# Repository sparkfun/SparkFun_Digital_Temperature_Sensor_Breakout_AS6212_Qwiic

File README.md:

SparkFun Digital Temperature Sensor Breakout - AS6212 (Qwiic)
========================================

[*SparkFun Digital Temperature Sensor Breakout - AS6212 (Qwiic)(SEN-18521)*](https://www.sparkfun.com/products/18521)

The AS6212 provides a combination of high temperature accuracy with excellent low power consumption using the AS6212 digital temperature sensor from ams AG. The AS6212 measures temperature with &plusmn;0.2&deg;C accuracy between -10&deg;C to 65&deg;C, consumes an average of 6&micro;A (0.1&micro;A in standby) and communicates over I<sup>2</sup>C so naturally we put it on a Qwiic breakout to add to our ever expanding Qwiic system. The sensor boasts a host of features including a configurable alert pin that can trigger when temperature data exceeds user-defined temperature thresholds. All of this in a tiny IC package measuring 1.5mm x 1mm.

The AD0 and AD1 jumpers control the I<sup>2</sup>C address as well as enabling/disabling the Alert pin. By default, these two-way jumpers connect the AD0 pin to Ground and the Alert/AD1 pin to 3.3V to enable the Alert pin and set the I<sup>2</sup>C address to 0x48. These jumpers control the address and enable/disable the Alert pin.

Repository Contents
-------------------

* **/Documentation** - Data sheets, additional product information
* **/Hardware** - Eagle design files (.brd, .sch)
* **/Production** - Production panel files (.brd)

Documentation
--------------

* **[Installing an Arduino Library Guide](https://learn.sparkfun.com/tutorials/installing-an-arduino-library)** - Basic information on how to install an Arduino library.
* **[SparkFun AS6212 Qwiic Arduino Library](https://github.com/sparkfun/SparkFun_AS6212_Qwiic_Arduino_Library)** - Arduino library for the SparkFun Digital Temperature Sensor Breakout - AS6212 (Qwiic).
* **[Qwiic AS6212 Py](https://github.com/sparkfun/Qwiic_AS6212_Py)** - Python module for the SparkFun Digital Temperature Sensor Breakout - AS6212 (Qwiic).
* **[Hookup Guide](https://learn.sparkfun.com/tutorials/digital-temperature-sensor-breakout---as6212-qwiic-hookup-guide)** - Basic hookup guide for the SparkFun Digital Temperature Sensor Breakout - AS6212 (Qwiic).

Version History
---------------

* [SEN-18521](https://www.sparkfun.com/products/18521) - Initial release of the SparkFun Digital Temperature Sensor Breakout - AS6212 (Qwiic).

License Information
-------------------

This product is _**open source**_! 

Please review the LICENSE.md file for license information. 

If you have any questions or concerns on licensing, please contact technical support on our [SparkFun forums](https://forum.sparkfun.com/viewforum.php?f=152).

Distributed as-is; no warranty is given.

- Your friends at SparkFun.

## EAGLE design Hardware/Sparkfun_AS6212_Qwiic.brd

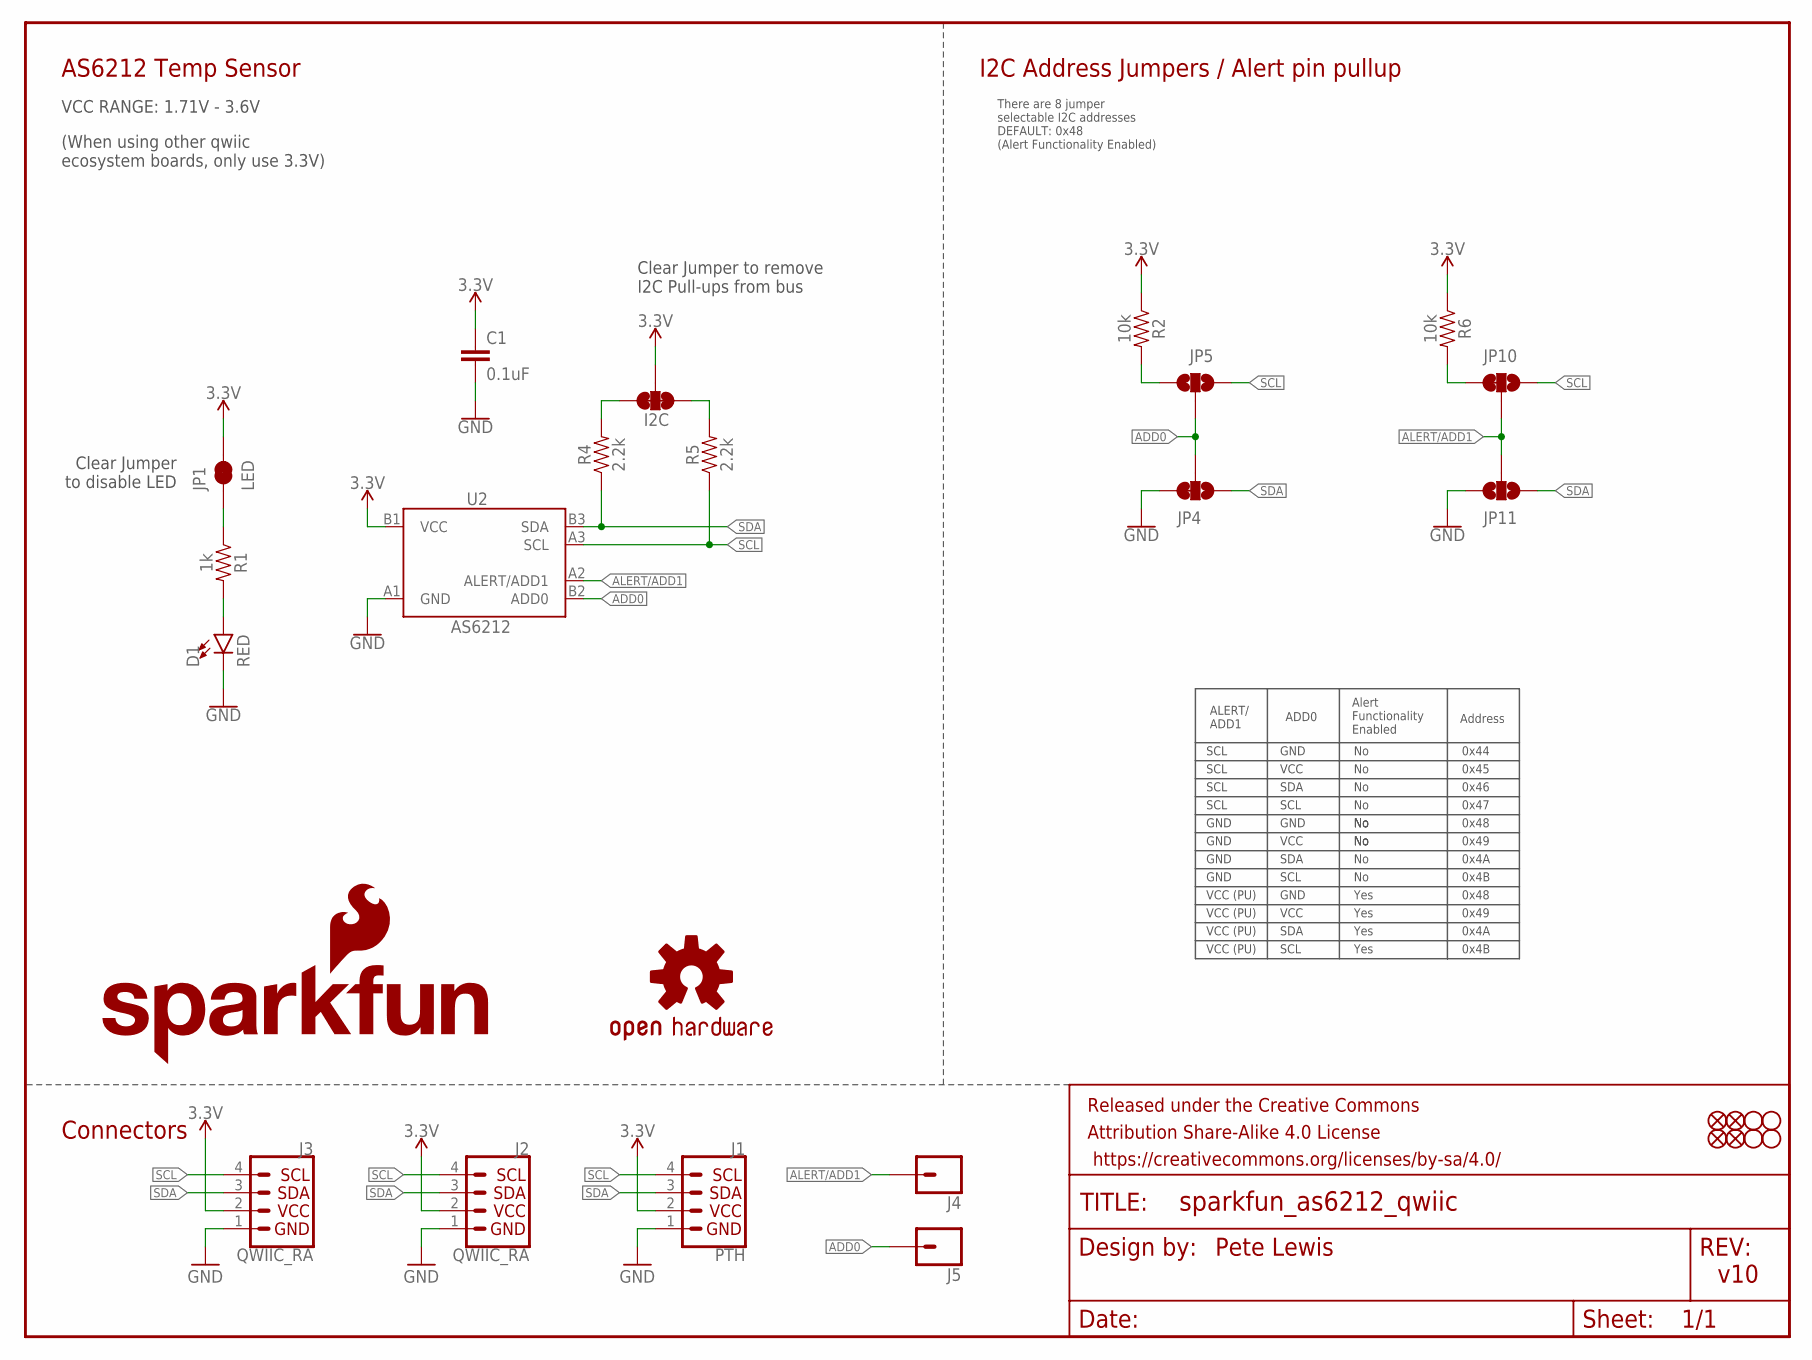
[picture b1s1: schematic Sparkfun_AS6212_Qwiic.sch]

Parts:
C1: 0.1uF; 0603
D1: RED; LED-0603
FD1, FD2, FD3, FD4: FIDUCIALUFIDUCIAL; FIDUCIAL-MICRO
FRAME1: FRAME-LETTER; CREATIVE_COMMONS
I2C: JUMPER-SMT_3_2-NC_TRACE_SILK; SMT-JUMPER_3_2-NC_TRACE_SILK
J1: PTH; 1X04_NO_SILK
J2, J3: QWIIC_RA; JST04_1MM_RA
J4, J5: CONN_01PTH_NO_SILK_YES_STOP; 1X01_NO_SILK
JP1: LED; SMT-JUMPER_2_NC_TRACE_SILK
JP2, JP3, JP8, JP9: STAND-OFF
JP4, JP10: JUMPER-SMT_3_1-NC_TRACE_NO-SILK; SMT-JUMPER_3_1-NC_TRACE_NO-SILK
JP5, JP11: JUMPER-SMT_3_NO_NO_SILK; SMT-JUMPER_3_0-NO_TRACE_NO-SILK
LOGO1: OSHW-LOGOMINI; OSHW-LOGO-MINI
LOGO4: SFE_LOGO_NAME_FLAME.1_INCH; SFE_LOGO_NAME_FLAME_.1
R1: 1k; 0603
R2, R6: 10k; 0603
R4, R5: 2.2k; 0603
U2: AS6212; WLCSP

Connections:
3.3V: C1.1, I2C.2, J1.2, J2.2, J3.2, JP1.2, R2.1, R6.1, U2.B1 (VCC)
ADD0: J5.1, JP4.2, JP5.2, U2.B2 (ADD0)
ALERT/ADD1: J4.1, JP10.2, JP11.2, U2.A2 (ALERT/ADD1)
GND: C1.2, D1.C, J1.1, J2.1, J3.1, JP4.3, JP11.3, U2.A1 (GND)
unnamed: D1.A, R1.2
unnamed: I2C.1, R5.2
unnamed: I2C.3, R4.2
unnamed: JP10.3, R6.2
unnamed: JP5.1, R2.2
unnamed: JP1.1, R1.1
SCL: J1.4, J2.4, J3.4, JP5.3, JP10.1, R5.1, U2.A3 (SCL)
SDA: J1.3, J2.3, J3.3, JP4.1, JP11.1, R4.1, U2.B3 (SDA)

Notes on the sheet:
Pete Lewis
Clear Jumper to remove I2C Pull-ups from bus
v10
There are 8 jumper selectable I2C addresses DEFAULT: 0x48 (Alert Functionality Enabled)
Alert Functionality Enabled
SCL
Clear Jumper to disable LED
VCC RANGE: 1.71V - 3.6V
(When using other qwiic ecosystem boards, only use 3.3V)
AS6212 Temp Sensor
I2C Address Jumpers / Alert pin pullup
Connectors
VCC (PU)
GND
ALERT/ ADD1
ADD0
SDA
VCC
Yes
Address
0x44
0x45
0x46
0x49
0x4A
0x4B
0x47
0x48

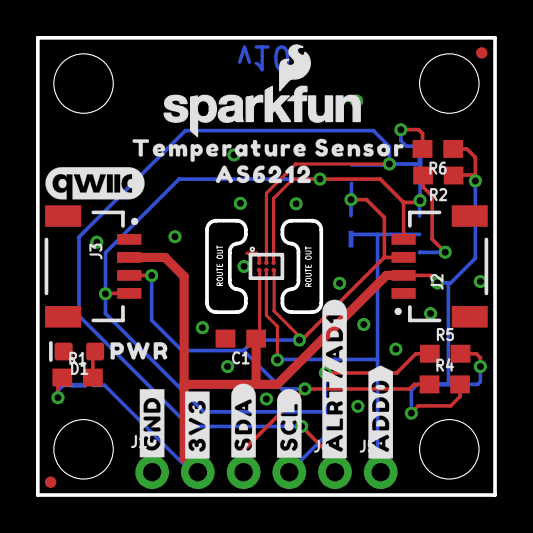
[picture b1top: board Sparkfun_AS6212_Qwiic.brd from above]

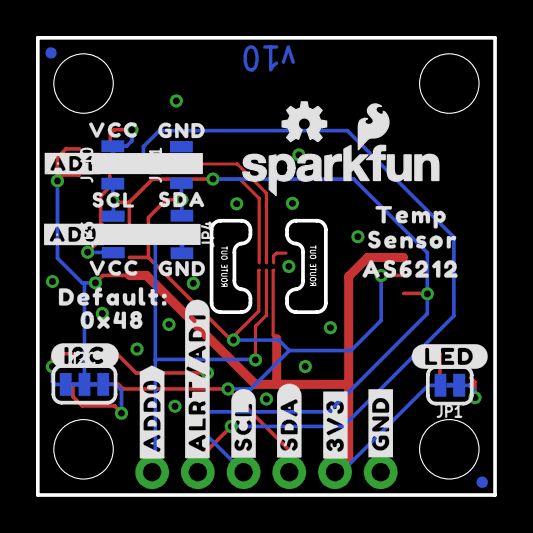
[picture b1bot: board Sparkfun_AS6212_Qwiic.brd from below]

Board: 2 copper layers, 25.4 x 25.4 mm, 62 parts (31 on the bottom side), 12 nets.

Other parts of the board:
LOGO2: SFE_LOGO_NAME_FLAME.1_INCH; SFE_LOGO_NAME_FLAME_.1
U$1: #LED#10
U$2: #I2C#11
U$3, U$25: AS62128
U$4: #AD0#1
U$5: #AD1#1
U$6: SCL3
U$7, U$13: VCC4
U$8: DEFAULT#11
U$9, U$14: GND5
U$10: SDA6
U$11, U$12: #ALRT#AD1#12
U$15: QWIIC_5.5MM
U$16: SENSOR8
U$17: TEMP9
U$18: 0X4812
U$19: PWR12
U$20, U$21: #3V3#13
U$24: TEMPERATURE_SENSOR7
U$26, U$30: #GND#62130
U$28, U$34: #SDA#62131
U$29, U$35: #SCL#62132
U$31, U$36: #ADD0#0

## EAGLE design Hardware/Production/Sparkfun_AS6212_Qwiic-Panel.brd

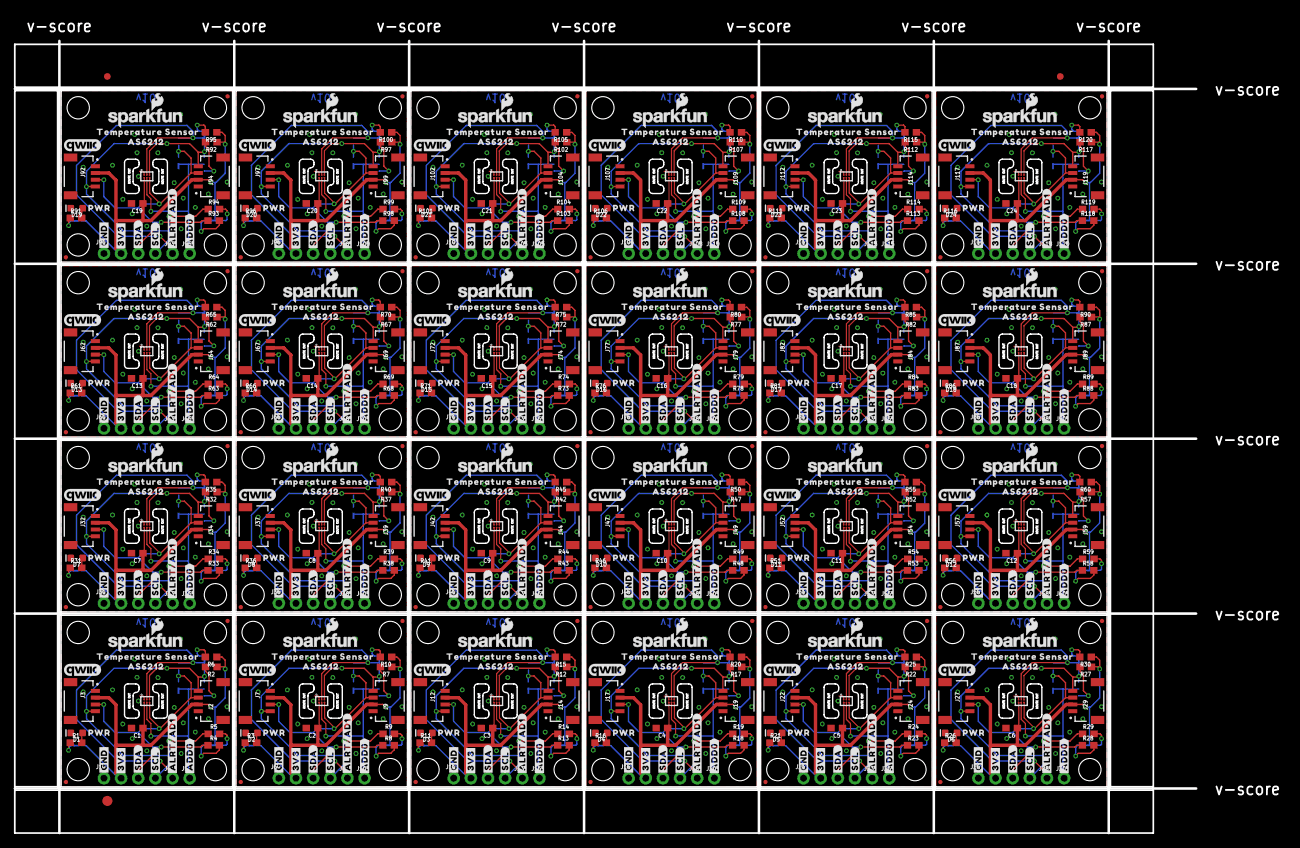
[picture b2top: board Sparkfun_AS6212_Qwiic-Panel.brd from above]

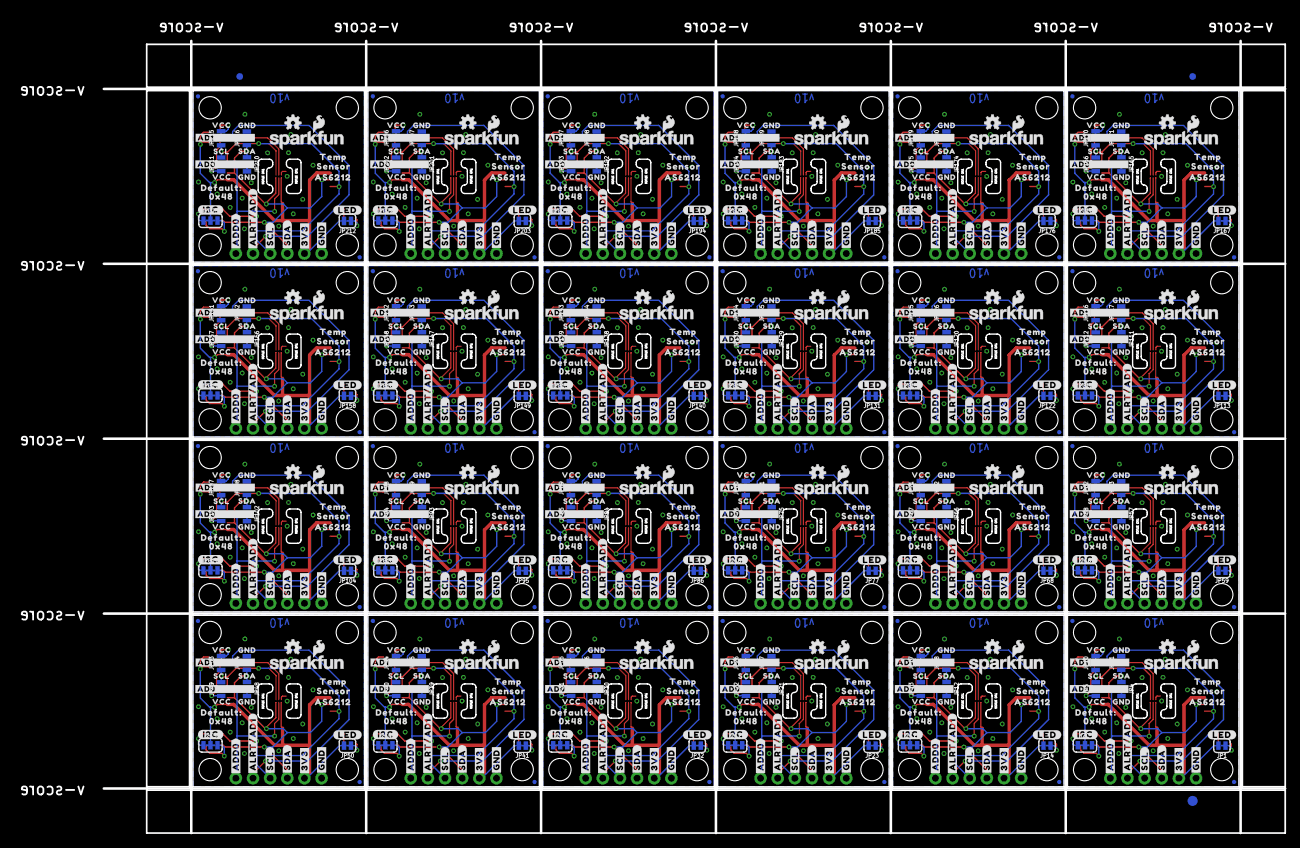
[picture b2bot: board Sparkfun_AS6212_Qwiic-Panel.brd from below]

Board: 2 copper layers, 188.2 x 121.2 mm, 1470 parts (747 on the bottom side), 288 nets.

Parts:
C1, C2, C3, C4, C5, C6, C7, C8, C9, C10, C11, C12, C13, C14, C15, C16, C17, C18, C19, C20, C21, C22, C23, C24: 0.1uF; 0603
D1, D2, D3, D4, D5, D6, D7, D8, D9, D10, D11, D12, D13, D14, D15, D16, D17, D18, D19, D20, D21, D22, D23, D24: RED; LED-0603
E$1, E$2, E$3, E$4: FIDUCIAL-1X2
E$5, E$6: FIDUCIAL-1.5X3
FD1, FD2, FD3, FD4, FD5, FD6, FD7, FD8, FD9, FD10, FD11, FD12, FD13, FD14, FD15, FD16, FD17, FD18, FD19, FD20, FD21, FD22, FD23, FD24, FD25, FD26, FD27, FD28, FD29, FD30, FD31, FD32, FD33, FD34, FD35, FD36, FD37, FD38, FD39, FD40, FD41, FD42, FD43, FD44, FD45, FD46, FD47, FD48, FD49, FD50, FD51, FD52, FD53, FD54, FD55, FD56, FD57, FD58, FD59, FD60, FD61, FD62, FD63, FD64, FD65, FD66, FD67, FD68, FD69, FD70, FD71, FD72, FD73, FD74, FD75, FD76, FD77, FD78, FD79, FD80, FD81, FD82, FD83, FD84, FD85, FD86, FD87, FD88, FD89, FD90, FD91, FD92, FD93, FD94, FD95, FD96: FIDUCIALUFIDUCIAL; FIDUCIAL-MICRO
I2C, I2C1, I2C2, I2C3, I2C4, I2C5, I2C6, I2C7, I2C8, I2C9, I2C10, I2C11, I2C12, I2C13, I2C14, I2C15, I2C16, I2C17, I2C18, I2C19, I2C20, I2C21, I2C22, I2C23: SMT-JUMPER_3_2-NC_TRACE_SILK
J1, J6, J11, J16, J21, J26, J31, J36, J41, J46, J51, J56, J61, J66, J71, J76, J81, J86, J91, J96, J101, J106, J111, J116: PTH; 1X04_NO_SILK
J2, J3, J7, J9, J12, J14, J17, J19, J22, J24, J27, J29, J32, J34, J37, J39, J42, J44, J47, J49, J52, J54, J57, J59, J62, J64, J67, J69, J72, J74, J77, J79, J82, J84, J87, J89, J92, J94, J97, J99, J102, J104, J107, J109, J112, J114, J117, J119: QWIIC_RA; JST04_1MM_RA
J4, J5, J8, J10, J13, J15, J18, J20, J23, J25, J28, J30, J33, J35, J38, J40, J43, J45, J48, J50, J53, J55, J58, J60, J63, J65, J68, J70, J73, J75, J78, J80, J83, J85, J88, J90, J93, J95, J98, J100, J103, J105, J108, J110, J113, J115, J118, J120: 1X01_NO_SILK
JP1, JP14, JP23, JP32, JP41, JP50, JP59, JP68, JP77, JP86, JP95, JP104, JP113, JP122, JP131, JP140, JP149, JP158, JP167, JP176, JP185, JP194, JP203, JP212: LED; SMT-JUMPER_2_NC_TRACE_SILK
JP2, JP3, JP6, JP7, JP8, JP9, JP15, JP16, JP19, JP20, JP24, JP25, JP28, JP29, JP33, JP34, JP37, JP38, JP42, JP43, JP46, JP47, JP51, JP52, JP55, JP56, JP60, JP61, JP64, JP65, JP69, JP70, JP73, JP74, JP78, JP79, JP82, JP83, JP87, JP88, JP91, JP92, JP96, JP97, JP100, JP101, JP105, JP106, JP109, JP110, JP114, JP115, JP118, JP119, JP123, JP124, JP127, JP128, JP132, JP133, JP136, JP137, JP141, JP142, JP145, JP146, JP150, JP151, JP154, JP155, JP159, JP160, JP163, JP164, JP168, JP169, JP172, JP173, JP177, JP178, JP181, JP182, JP186, JP187, JP190, JP191, JP195, JP196, JP199, JP200, JP204, JP205, JP208, JP209, JP213, JP214: STAND-OFF
JP4, JP10, JP12, JP17, JP21, JP26, JP30, JP35, JP39, JP44, JP48, JP53, JP57, JP62, JP66, JP71, JP75, JP80, JP84, JP89, JP93, JP98, JP102, JP107, JP111, JP116, JP120, JP125, JP129, JP134, JP138, JP143, JP147, JP152, JP156, JP161, JP165, JP170, JP174, JP179, JP183, JP188, JP192, JP197, JP201, JP206, JP210, JP215: JUMPER-SMT_3_1-NC_TRACE_NO-SILK; SMT-JUMPER_3_1-NC_TRACE_NO-SILK
JP5, JP11, JP13, JP18, JP22, JP27, JP31, JP36, JP40, JP45, JP49, JP54, JP58, JP63, JP67, JP72, JP76, JP81, JP85, JP90, JP94, JP99, JP103, JP108, JP112, JP117, JP121, JP126, JP130, JP135, JP139, JP144, JP148, JP153, JP157, JP162, JP166, JP171, JP175, JP180, JP184, JP189, JP193, JP198, JP202, JP207, JP211, JP216: JUMPER-SMT_3_NO_NO_SILK; SMT-JUMPER_3_0-NO_TRACE_NO-SILK
LOGO1, LOGO3, LOGO7, LOGO10, LOGO13, LOGO16, LOGO19, LOGO22, LOGO25, LOGO28, LOGO31, LOGO34, LOGO37, LOGO40, LOGO43, LOGO46, LOGO49, LOGO52, LOGO55, LOGO58, LOGO61, LOGO64, LOGO67, LOGO70: OSHW-LOGOMINI; OSHW-LOGO-MINI
LOGO2, LOGO4, LOGO5, LOGO6, LOGO8, LOGO9, LOGO11, LOGO12, LOGO14, LOGO15, LOGO17, LOGO18, LOGO20, LOGO21, LOGO23, LOGO24, LOGO26, LOGO27, LOGO29, LOGO30, LOGO32, LOGO33, LOGO35, LOGO36, LOGO38, LOGO39, LOGO41, LOGO42, LOGO44, LOGO45, LOGO47, LOGO48, LOGO50, LOGO51, LOGO53, LOGO54, LOGO56, LOGO57, LOGO59, LOGO60, LOGO62, LOGO63, LOGO65, LOGO66, LOGO68, LOGO69, LOGO71, LOGO72: SFE_LOGO_NAME_FLAME.1_INCH; SFE_LOGO_NAME_FLAME_.1
R1, R3, R11, R16, R21, R26, R31, R36, R41, R46, R51, R56, R61, R66, R71, R76, R81, R86, R91, R96, R101, R106, R111, R116: 1k; 0603
R2, R6, R7, R10, R12, R15, R17, R20, R22, R25, R27, R30, R32, R35, R37, R40, R42, R45, R47, R50, R52, R55, R57, R60, R62, R65, R67, R70, R72, R75, R77, R80, R82, R85, R87, R90, R92, R95, R97, R100, R102, R105, R107, R110, R112, R115, R117, R120: 10k; 0603
R4, R5, R8, R9, R13, R14, R18, R19, R23, R24, R28, R29, R33, R34, R38, R39, R43, R44, R48, R49, R53, R54, R58, R59, R63, R64, R68, R69, R73, R74, R78, R79, R83, R84, R88, R89, R93, R94, R98, R99, R103, R104, R108, R109, R113, R114, R118, R119: 2.2k; 0603
U1, U2, U3, U4, U5, U6, U7, U8, U9, U10, U11, U12, U13, U14, U15, U16, U17, U18, U19, U20, U21, U22, U23, U24: AS6212; WLCSP
U$1, U$54, U$85, U$116, U$147, U$178, U$209, U$240, U$271, U$302, U$333, U$364, U$395, U$426, U$457, U$488, U$519, U$550, U$581, U$612, U$643, U$674, U$705, U$736: #LED#10
U$2, U$55, U$86, U$117, U$148, U$179, U$210, U$241, U$272, U$303, U$334, U$365, U$396, U$427, U$458, U$489, U$520, U$551, U$582, U$613, U$644, U$675, U$706, U$737: #I2C#11
U$3, U$25, U$27, U$43, U$65, U$74, U$96, U$105, U$127, U$136, U$158, U$167, U$189, U$198, U$220, U$229, U$251, U$260, U$282, U$291, U$313, U$322, U$344, U$353, U$375, U$384, U$406, U$415, U$437, U$446, U$468, U$477, U$499, U$508, U$530, U$539, U$561, U$570, U$592, U$601, U$623, U$632, U$654, U$663, U$685, U$694, U$716, U$725: AS62128
U$4, U$44, U$75, U$106, U$137, U$168, U$199, U$230, U$261, U$292, U$323, U$354, U$385, U$416, U$447, U$478, U$509, U$540, U$571, U$602, U$633, U$664, U$695, U$726: #AD0#1
U$5, U$45, U$76, U$107, U$138, U$169, U$200, U$231, U$262, U$293, U$324, U$355, U$386, U$417, U$448, U$479, U$510, U$541, U$572, U$603, U$634, U$665, U$696, U$727: #AD1#1
U$6, U$46, U$77, U$108, U$139, U$170, U$201, U$232, U$263, U$294, U$325, U$356, U$387, U$418, U$449, U$480, U$511, U$542, U$573, U$604, U$635, U$666, U$697, U$728: SCL3
U$7, U$13, U$47, U$50, U$78, U$81, U$109, U$112, U$140, U$143, U$171, U$174, U$202, U$205, U$233, U$236, U$264, U$267, U$295, U$298, U$326, U$329, U$357, U$360, U$388, U$391, U$419, U$422, U$450, U$453, U$481, U$484, U$512, U$515, U$543, U$546, U$574, U$577, U$605, U$608, U$636, U$639, U$667, U$670, U$698, U$701, U$729, U$732: VCC4
U$8, U$56, U$87, U$118, U$149, U$180, U$211, U$242, U$273, U$304, U$335, U$366, U$397, U$428, U$459, U$490, U$521, U$552, U$583, U$614, U$645, U$676, U$707, U$738: DEFAULT#11
U$9, U$14, U$48, U$51, U$79, U$82, U$110, U$113, U$141, U$144, U$172, U$175, U$203, U$206, U$234, U$237, U$265, U$268, U$296, U$299, U$327, U$330, U$358, U$361, U$389, U$392, U$420, U$423, U$451, U$454, U$482, U$485, U$513, U$516, U$544, U$547, U$575, U$578, U$606, U$609, U$637, U$640, U$668, U$671, U$699, U$702, U$730, U$733: GND5
U$10, U$49, U$80, U$111, U$142, U$173, U$204, U$235, U$266, U$297, U$328, U$359, U$390, U$421, U$452, U$483, U$514, U$545, U$576, U$607, U$638, U$669, U$700, U$731: SDA6
U$11, U$12, U$58, U$59, U$89, U$90, U$120, U$121, U$151, U$152, U$182, U$183, U$213, U$214, U$244, U$245, U$275, U$276, U$306, U$307, U$337, U$338, U$368, U$369, U$399, U$400, U$430, U$431, U$461, U$462, U$492, U$493, U$523, U$524, U$554, U$555, U$585, U$586, U$616, U$617, U$647, U$648, U$678, U$679, U$709, U$710, U$740, U$741: #ALRT#AD1#12
U$15, U$22, U$63, U$94, U$125, U$156, U$187, U$218, U$249, U$280, U$311, U$342, U$373, U$404, U$435, U$466, U$497, U$528, U$559, U$590, U$621, U$652, U$683, U$714: QWIIC_5.5MM
U$16, U$52, U$83, U$114, U$145, U$176, U$207, U$238, U$269, U$300, U$331, U$362, U$393, U$424, U$455, U$486, U$517, U$548, U$579, U$610, U$641, U$672, U$703, U$734: SENSOR8
U$17, U$53, U$84, U$115, U$146, U$177, U$208, U$239, U$270, U$301, U$332, U$363, U$394, U$425, U$456, U$487, U$518, U$549, U$580, U$611, U$642, U$673, U$704, U$735: TEMP9
U$18, U$57, U$88, U$119, U$150, U$181, U$212, U$243, U$274, U$305, U$336, U$367, U$398, U$429, U$460, U$491, U$522, U$553, U$584, U$615, U$646, U$677, U$708, U$739: 0X4812
U$19, U$60, U$91, U$122, U$153, U$184, U$215, U$246, U$277, U$308, U$339, U$370, U$401, U$432, U$463, U$494, U$525, U$556, U$587, U$618, U$649, U$680, U$711, U$742: PWR12
U$20, U$21, U$61, U$62, U$92, U$93, U$123, U$124, U$154, U$155, U$185, U$186, U$216, U$217, U$247, U$248, U$278, U$279, U$309, U$310, U$340, U$341, U$371, U$372, U$402, U$403, U$433, U$434, U$464, U$465, U$495, U$496, U$526, U$527, U$557, U$558, U$588, U$589, U$619, U$620, U$650, U$651, U$681, U$682, U$712, U$713, U$743, U$744: #3V3#13
U$23, U$24, U$64, U$95, U$126, U$157, U$188, U$219, U$250, U$281, U$312, U$343, U$374, U$405, U$436, U$467, U$498, U$529, U$560, U$591, U$622, U$653, U$684, U$715: TEMPERATURE_SENSOR7
U$26, U$30, U$32, U$39, U$66, U$70, U$97, U$101, U$128, U$132, U$159, U$163, U$190, U$194, U$221, U$225, U$252, U$256, U$283, U$287, U$314, U$318, U$345, U$349, U$376, U$380, U$407, U$411, U$438, U$442, U$469, U$473, U$500, U$504, U$531, U$535, U$562, U$566, U$593, U$597, U$624, U$628, U$655, U$659, U$686, U$690, U$717, U$721: #GND#62130
U$28, U$33, U$34, U$40, U$67, U$71, U$98, U$102, U$129, U$133, U$160, U$164, U$191, U$195, U$222, U$226, U$253, U$257, U$284, U$288, U$315, U$319, U$346, U$350, U$377, U$381, U$408, U$412, U$439, U$443, U$470, U$474, U$501, U$505, U$532, U$536, U$563, U$567, U$594, U$598, U$625, U$629, U$656, U$660, U$687, U$691, U$718, U$722: #SDA#62131
U$29, U$35, U$37, U$41, U$68, U$72, U$99, U$103, U$130, U$134, U$161, U$165, U$192, U$196, U$223, U$227, U$254, U$258, U$285, U$289, U$316, U$320, U$347, U$351, U$378, U$382, U$409, U$413, U$440, U$444, U$471, U$475, U$502, U$506, U$533, U$537, U$564, U$568, U$595, U$599, U$626, U$630, U$657, U$661, U$688, U$692, U$719, U$723: #SCL#62132
U$31, U$36, U$38, U$42, U$69, U$73, U$100, U$104, U$131, U$135, U$162, U$166, U$193, U$197, U$224, U$228, U$255, U$259, U$286, U$290, U$317, U$321, U$348, U$352, U$379, U$383, U$410, U$414, U$441, U$445, U$472, U$476, U$503, U$507, U$534, U$538, U$565, U$569, U$596, U$600, U$627, U$631, U$658, U$662, U$689, U$693, U$720, U$724: #ADD0#0

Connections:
3.3V: C1.1, I2C.2, J1.2, J2.2, J3.2, JP1.2, R2.1, R6.1, U2.B1
3.3V1: C2.1, I2C1.2, J6.2, J7.2, J9.2, JP14.2, R7.1, R10.1, U1.B1
3.3V2: C3.1, I2C2.2, J11.2, J12.2, J14.2, JP23.2, R12.1, R15.1, U3.B1
3.3V3: C4.1, I2C3.2, J16.2, J17.2, J19.2, JP32.2, R17.1, R20.1, U4.B1
3.3V4: C5.1, I2C4.2, J21.2, J22.2, J24.2, JP41.2, R22.1, R25.1, U5.B1
3.3V5: C6.1, I2C5.2, J26.2, J27.2, J29.2, JP50.2, R27.1, R30.1, U6.B1
3.3V6: C7.1, I2C6.2, J31.2, J32.2, J34.2, JP59.2, R32.1, R35.1, U7.B1
3.3V7: C8.1, I2C7.2, J36.2, J37.2, J39.2, JP68.2, R37.1, R40.1, U8.B1
3.3V8: C9.1, I2C8.2, J41.2, J42.2, J44.2, JP77.2, R42.1, R45.1, U9.B1
3.3V9: C10.1, I2C9.2, J46.2, J47.2, J49.2, JP86.2, R47.1, R50.1, U10.B1
3.3V10: C11.1, I2C10.2, J51.2, J52.2, J54.2, JP95.2, R52.1, R55.1, U11.B1
3.3V11: C12.1, I2C11.2, J56.2, J57.2, J59.2, JP104.2, R57.1, R60.1, U12.B1
3.3V12: C13.1, I2C12.2, J61.2, J62.2, J64.2, JP113.2, R62.1, R65.1, U13.B1
3.3V13: C14.1, I2C13.2, J66.2, J67.2, J69.2, JP122.2, R67.1, R70.1, U14.B1
3.3V14: C15.1, I2C14.2, J71.2, J72.2, J74.2, JP131.2, R72.1, R75.1, U15.B1
3.3V15: C16.1, I2C15.2, J76.2, J77.2, J79.2, JP140.2, R77.1, R80.1, U16.B1
3.3V16: C17.1, I2C16.2, J81.2, J82.2, J84.2, JP149.2, R82.1, R85.1, U17.B1
3.3V17: C18.1, I2C17.2, J86.2, J87.2, J89.2, JP158.2, R87.1, R90.1, U18.B1
3.3V18: C19.1, I2C18.2, J91.2, J92.2, J94.2, JP167.2, R92.1, R95.1, U19.B1
3.3V19: C20.1, I2C19.2, J96.2, J97.2, J99.2, JP176.2, R97.1, R100.1, U20.B1
3.3V20: C21.1, I2C20.2, J101.2, J102.2, J104.2, JP185.2, R102.1, R105.1, U21.B1
3.3V21: C22.1, I2C21.2, J106.2, J107.2, J109.2, JP194.2, R107.1, R110.1, U22.B1
3.3V22: C23.1, I2C22.2, J111.2, J112.2, J114.2, JP203.2, R112.1, R115.1, U23.B1
3.3V23: C24.1, I2C23.2, J116.2, J117.2, J119.2, JP212.2, R117.1, R120.1, U24.B1
ADD0: J5.1, JP4.2, JP5.2, U2.B2
ADD1: J10.1, JP12.2, JP13.2, U1.B2
ADD2: J15.1, JP21.2, JP22.2, U3.B2
ADD3: J20.1, JP30.2, JP31.2, U4.B2
ADD4: J25.1, JP39.2, JP40.2, U5.B2
ADD5: J30.1, JP48.2, JP49.2, U6.B2
ADD6: J35.1, JP57.2, JP58.2, U7.B2
ADD7: J40.1, JP66.2, JP67.2, U8.B2
ADD8: J45.1, JP75.2, JP76.2, U9.B2
ADD9: J50.1, JP84.2, JP85.2, U10.B2
ADD10: J55.1, JP93.2, JP94.2, U11.B2
ADD11: J60.1, JP102.2, JP103.2, U12.B2
ADD12: J65.1, JP111.2, JP112.2, U13.B2
ADD13: J70.1, JP120.2, JP121.2, U14.B2
ADD14: J75.1, JP129.2, JP130.2, U15.B2
ADD15: J80.1, JP138.2, JP139.2, U16.B2
ADD16: J85.1, JP147.2, JP148.2, U17.B2
ADD17: J90.1, JP156.2, JP157.2, U18.B2
ADD18: J95.1, JP165.2, JP166.2, U19.B2
ADD19: J100.1, JP174.2, JP175.2, U20.B2
ADD20: J105.1, JP183.2, JP184.2, U21.B2
ADD21: J110.1, JP192.2, JP193.2, U22.B2
ADD22: J115.1, JP201.2, JP202.2, U23.B2
ADD23: J120.1, JP210.2, JP211.2, U24.B2
ALERT/ADD1: J4.1, JP10.2, JP11.2, U2.A2
ALERT/ADD2: J8.1, JP17.2, JP18.2, U1.A2
ALERT/ADD3: J13.1, JP26.2, JP27.2, U3.A2
ALERT/ADD4: J18.1, JP35.2, JP36.2, U4.A2
ALERT/ADD5: J23.1, JP44.2, JP45.2, U5.A2
ALERT/ADD6: J28.1, JP53.2, JP54.2, U6.A2
ALERT/ADD7: J33.1, JP62.2, JP63.2, U7.A2
ALERT/ADD8: J38.1, JP71.2, JP72.2, U8.A2
ALERT/ADD9: J43.1, JP80.2, JP81.2, U9.A2
ALERT/ADD10: J48.1, JP89.2, JP90.2, U10.A2
ALERT/ADD11: J53.1, JP98.2, JP99.2, U11.A2
ALERT/ADD12: J58.1, JP107.2, JP108.2, U12.A2
ALERT/ADD13: J63.1, JP116.2, JP117.2, U13.A2
ALERT/ADD14: J68.1, JP125.2, JP126.2, U14.A2
ALERT/ADD15: J73.1, JP134.2, JP135.2, U15.A2
ALERT/ADD16: J78.1, JP143.2, JP144.2, U16.A2
ALERT/ADD17: J83.1, JP152.2, JP153.2, U17.A2
ALERT/ADD18: J88.1, JP161.2, JP162.2, U18.A2
ALERT/ADD19: J93.1, JP170.2, JP171.2, U19.A2
ALERT/ADD20: J98.1, JP179.2, JP180.2, U20.A2
ALERT/ADD21: J103.1, JP188.2, JP189.2, U21.A2
ALERT/ADD22: J108.1, JP197.2, JP198.2, U22.A2
ALERT/ADD23: J113.1, JP206.2, JP207.2, U23.A2
ALERT/ADD24: J118.1, JP215.2, JP216.2, U24.A2
GND: C1.2, D1.C, J1.1, J2.1, J3.1, JP4.3, JP11.3, U2.A1
GND1: C2.2, D2.C, J6.1, J7.1, J9.1, JP12.3, JP18.3, U1.A1
GND2: C3.2, D3.C, J11.1, J12.1, J14.1, JP21.3, JP27.3, U3.A1
GND3: C4.2, D4.C, J16.1, J17.1, J19.1, JP30.3, JP36.3, U4.A1
GND4: C5.2, D5.C, J21.1, J22.1, J24.1, JP39.3, JP45.3, U5.A1
GND5: C6.2, D6.C, J26.1, J27.1, J29.1, JP48.3, JP54.3, U6.A1
GND6: C7.2, D7.C, J31.1, J32.1, J34.1, JP57.3, JP63.3, U7.A1
GND7: C8.2, D8.C, J36.1, J37.1, J39.1, JP66.3, JP72.3, U8.A1
GND8: C9.2, D9.C, J41.1, J42.1, J44.1, JP75.3, JP81.3, U9.A1
GND9: C10.2, D10.C, J46.1, J47.1, J49.1, JP84.3, JP90.3, U10.A1
GND10: C11.2, D11.C, J51.1, J52.1, J54.1, JP93.3, JP99.3, U11.A1
GND11: C12.2, D12.C, J56.1, J57.1, J59.1, JP102.3, JP108.3, U12.A1
GND12: C13.2, D13.C, J61.1, J62.1, J64.1, JP111.3, JP117.3, U13.A1
GND13: C14.2, D14.C, J66.1, J67.1, J69.1, JP120.3, JP126.3, U14.A1
GND14: C15.2, D15.C, J71.1, J72.1, J74.1, JP129.3, JP135.3, U15.A1
GND15: C16.2, D16.C, J76.1, J77.1, J79.1, JP138.3, JP144.3, U16.A1
GND16: C17.2, D17.C, J81.1, J82.1, J84.1, JP147.3, JP153.3, U17.A1
GND17: C18.2, D18.C, J86.1, J87.1, J89.1, JP156.3, JP162.3, U18.A1
GND18: C19.2, D19.C, J91.1, J92.1, J94.1, JP165.3, JP171.3, U19.A1
GND19: C20.2, D20.C, J96.1, J97.1, J99.1, JP174.3, JP180.3, U20.A1
GND20: C21.2, D21.C, J101.1, J102.1, J104.1, JP183.3, JP189.3, U21.A1
GND21: C22.2, D22.C, J106.1, J107.1, J109.1, JP192.3, JP198.3, U22.A1
GND22: C23.2, D23.C, J111.1, J112.1, J114.1, JP201.3, JP207.3, U23.A1
GND23: C24.2, D24.C, J116.1, J117.1, J119.1, JP210.3, JP216.3, U24.A1
unnamed: D1.A, R1.2
unnamed: I2C.1, R5.2
unnamed: I2C.3, R4.2
unnamed: D2.A, R3.2
unnamed: JP10.3, R6.2
unnamed: I2C1.1, R9.2
unnamed: JP5.1, R2.2
unnamed: JP1.1, R1.1
unnamed: I2C1.3, R8.2
unnamed: JP13.1, R7.2
unnamed: JP14.1, R3.1
unnamed: JP17.3, R10.2
unnamed: D3.A, R11.2
unnamed: I2C2.1, R14.2
unnamed: I2C2.3, R13.2
unnamed: JP22.1, R12.2
unnamed: JP23.1, R11.1
unnamed: JP26.3, R15.2
unnamed: D4.A, R16.2
unnamed: I2C3.1, R19.2
unnamed: I2C3.3, R18.2
unnamed: JP31.1, R17.2
unnamed: JP32.1, R16.1
unnamed: JP35.3, R20.2
unnamed: D5.A, R21.2
unnamed: I2C4.1, R24.2
unnamed: I2C4.3, R23.2
unnamed: JP40.1, R22.2
unnamed: JP41.1, R21.1
unnamed: JP44.3, R25.2
unnamed: D6.A, R26.2
unnamed: I2C5.1, R29.2
unnamed: I2C5.3, R28.2
unnamed: JP49.1, R27.2
unnamed: JP50.1, R26.1
unnamed: JP53.3, R30.2
unnamed: D7.A, R31.2
unnamed: I2C6.1, R34.2
unnamed: I2C6.3, R33.2
unnamed: JP58.1, R32.2
unnamed: JP59.1, R31.1
unnamed: JP62.3, R35.2
unnamed: D8.A, R36.2
unnamed: I2C7.1, R39.2
unnamed: I2C7.3, R38.2
unnamed: JP67.1, R37.2
unnamed: JP68.1, R36.1
unnamed: JP71.3, R40.2
unnamed: D9.A, R41.2
unnamed: I2C8.1, R44.2
unnamed: I2C8.3, R43.2
unnamed: JP76.1, R42.2
unnamed: JP77.1, R41.1
unnamed: JP80.3, R45.2
unnamed: D10.A, R46.2
unnamed: I2C9.1, R49.2
unnamed: I2C9.3, R48.2
unnamed: JP85.1, R47.2
unnamed: JP86.1, R46.1
unnamed: JP89.3, R50.2
unnamed: D11.A, R51.2
unnamed: I2C10.1, R54.2
unnamed: I2C10.3, R53.2
unnamed: JP94.1, R52.2
unnamed: JP95.1, R51.1
unnamed: JP98.3, R55.2
unnamed: D12.A, R56.2
unnamed: I2C11.1, R59.2
unnamed: I2C11.3, R58.2
unnamed: JP103.1, R57.2
unnamed: JP104.1, R56.1
unnamed: JP107.3, R60.2
unnamed: D13.A, R61.2
unnamed: I2C12.1, R64.2
unnamed: I2C12.3, R63.2
unnamed: JP112.1, R62.2
unnamed: JP113.1, R61.1
unnamed: JP116.3, R65.2
unnamed: D14.A, R66.2
unnamed: I2C13.1, R69.2
unnamed: I2C13.3, R68.2
unnamed: JP121.1, R67.2
unnamed: JP122.1, R66.1
unnamed: JP125.3, R70.2
unnamed: D15.A, R71.2
unnamed: I2C14.1, R74.2
unnamed: I2C14.3, R73.2
unnamed: JP130.1, R72.2
unnamed: JP131.1, R71.1
unnamed: JP134.3, R75.2
unnamed: D16.A, R76.2
unnamed: I2C15.1, R79.2
unnamed: I2C15.3, R78.2
unnamed: JP139.1, R77.2
unnamed: JP140.1, R76.1
unnamed: JP143.3, R80.2
unnamed: D17.A, R81.2
unnamed: I2C16.1, R84.2
unnamed: I2C16.3, R83.2
unnamed: JP148.1, R82.2
unnamed: JP149.1, R81.1
unnamed: JP152.3, R85.2
unnamed: D18.A, R86.2
unnamed: I2C17.1, R89.2
unnamed: I2C17.3, R88.2
unnamed: JP157.1, R87.2
unnamed: JP158.1, R86.1
unnamed: JP161.3, R90.2
unnamed: D19.A, R91.2
unnamed: I2C18.1, R94.2
unnamed: I2C18.3, R93.2
unnamed: JP166.1, R92.2
unnamed: JP167.1, R91.1
unnamed: JP170.3, R95.2
unnamed: D20.A, R96.2
unnamed: I2C19.1, R99.2
unnamed: I2C19.3, R98.2
unnamed: JP175.1, R97.2
unnamed: JP176.1, R96.1
unnamed: JP179.3, R100.2
unnamed: D21.A, R101.2
unnamed: I2C20.1, R104.2
unnamed: I2C20.3, R103.2
unnamed: JP184.1, R102.2
unnamed: JP185.1, R101.1
unnamed: JP188.3, R105.2
unnamed: D22.A, R106.2
unnamed: I2C21.1, R109.2
unnamed: I2C21.3, R108.2
unnamed: JP193.1, R107.2
unnamed: JP194.1, R106.1
unnamed: JP197.3, R110.2
unnamed: D23.A, R111.2
unnamed: I2C22.1, R114.2
unnamed: I2C22.3, R113.2
unnamed: JP202.1, R112.2
unnamed: JP203.1, R111.1
unnamed: JP206.3, R115.2
unnamed: D24.A, R116.2
unnamed: I2C23.1, R119.2
unnamed: I2C23.3, R118.2
unnamed: JP211.1, R117.2
unnamed: JP212.1, R116.1
unnamed: JP215.3, R120.2
SCL: J1.4, J2.4, J3.4, JP5.3, JP10.1, R5.1, U2.A3
SCL1: J6.4, J7.4, J9.4, JP13.3, JP17.1, R9.1, U1.A3
SCL2: J11.4, J12.4, J14.4, JP22.3, JP26.1, R14.1, U3.A3
SCL3: J16.4, J17.4, J19.4, JP31.3, JP35.1, R19.1, U4.A3
SCL4: J21.4, J22.4, J24.4, JP40.3, JP44.1, R24.1, U5.A3
SCL5: J26.4, J27.4, J29.4, JP49.3, JP53.1, R29.1, U6.A3
SCL6: J31.4, J32.4, J34.4, JP58.3, JP62.1, R34.1, U7.A3
SCL7: J36.4, J37.4, J39.4, JP67.3, JP71.1, R39.1, U8.A3
SCL8: J41.4, J42.4, J44.4, JP76.3, JP80.1, R44.1, U9.A3
SCL9: J46.4, J47.4, J49.4, JP85.3, JP89.1, R49.1, U10.A3
SCL10: J51.4, J52.4, J54.4, JP94.3, JP98.1, R54.1, U11.A3
SCL11: J56.4, J57.4, J59.4, JP103.3, JP107.1, R59.1, U12.A3
SCL12: J61.4, J62.4, J64.4, JP112.3, JP116.1, R64.1, U13.A3
SCL13: J66.4, J67.4, J69.4, JP121.3, JP125.1, R69.1, U14.A3
SCL14: J71.4, J72.4, J74.4, JP130.3, JP134.1, R74.1, U15.A3
SCL15: J76.4, J77.4, J79.4, JP139.3, JP143.1, R79.1, U16.A3
SCL16: J81.4, J82.4, J84.4, JP148.3, JP152.1, R84.1, U17.A3
SCL17: J86.4, J87.4, J89.4, JP157.3, JP161.1, R89.1, U18.A3
SCL18: J91.4, J92.4, J94.4, JP166.3, JP170.1, R94.1, U19.A3
SCL19: J96.4, J97.4, J99.4, JP175.3, JP179.1, R99.1, U20.A3
SCL20: J101.4, J102.4, J104.4, JP184.3, JP188.1, R104.1, U21.A3
SCL21: J106.4, J107.4, J109.4, JP193.3, JP197.1, R109.1, U22.A3
SCL22: J111.4, J112.4, J114.4, JP202.3, JP206.1, R114.1, U23.A3
SCL23: J116.4, J117.4, J119.4, JP211.3, JP215.1, R119.1, U24.A3
SDA: J1.3, J2.3, J3.3, JP4.1, JP11.1, R4.1, U2.B3
SDA1: J6.3, J7.3, J9.3, JP12.1, JP18.1, R8.1, U1.B3
SDA2: J11.3, J12.3, J14.3, JP21.1, JP27.1, R13.1, U3.B3
SDA3: J16.3, J17.3, J19.3, JP30.1, JP36.1, R18.1, U4.B3
SDA4: J21.3, J22.3, J24.3, JP39.1, JP45.1, R23.1, U5.B3
SDA5: J26.3, J27.3, J29.3, JP48.1, JP54.1, R28.1, U6.B3
SDA6: J31.3, J32.3, J34.3, JP57.1, JP63.1, R33.1, U7.B3
SDA7: J36.3, J37.3, J39.3, JP66.1, JP72.1, R38.1, U8.B3
SDA8: J41.3, J42.3, J44.3, JP75.1, JP81.1, R43.1, U9.B3
SDA9: J46.3, J47.3, J49.3, JP84.1, JP90.1, R48.1, U10.B3
SDA10: J51.3, J52.3, J54.3, JP93.1, JP99.1, R53.1, U11.B3
SDA11: J56.3, J57.3, J59.3, JP102.1, JP108.1, R58.1, U12.B3
SDA12: J61.3, J62.3, J64.3, JP111.1, JP117.1, R63.1, U13.B3
SDA13: J66.3, J67.3, J69.3, JP120.1, JP126.1, R68.1, U14.B3
SDA14: J71.3, J72.3, J74.3, JP129.1, JP135.1, R73.1, U15.B3
SDA15: J76.3, J77.3, J79.3, JP138.1, JP144.1, R78.1, U16.B3
SDA16: J81.3, J82.3, J84.3, JP147.1, JP153.1, R83.1, U17.B3
SDA17: J86.3, J87.3, J89.3, JP156.1, JP162.1, R88.1, U18.B3
SDA18: J91.3, J92.3, J94.3, JP165.1, JP171.1, R93.1, U19.B3
SDA19: J96.3, J97.3, J99.3, JP174.1, JP180.1, R98.1, U20.B3
SDA20: J101.3, J102.3, J104.3, JP183.1, JP189.1, R103.1, U21.B3
SDA21: J106.3, J107.3, J109.3, JP192.1, JP198.1, R108.1, U22.B3
SDA22: J111.3, J112.3, J114.3, JP201.1, JP207.1, R113.1, U23.B3
SDA23: J116.3, J117.3, J119.3, JP210.1, JP216.1, R118.1, U24.B3

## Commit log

2021-07-21 Layout started
2021-07-21 Layout ready for review
2021-07-22 my run of checklist catches
    -silk outline of IC package increased to 8 mil
    -approved DRC errors
    -re-routed off IS to allow GND flow
    -more GND stiching vias
    -nudged some resistors away from standoff screw head
    -updated 3-pad jumpers to latest in library to avoid access DRC errors
2021-07-22 design review group
    -adjusted some traces and added more GND vias for return currents
    -changed to 3V3 on label to avoid dot not printing nice
    -GND symbols updated to new libraries
2021-07-22 removed old milling stuff for air gaps
2021-07-22 nudged LED and I2C jumpers away from standoffs a tiny bit.
2021-07-22 Production panel and gerbers v10
2021-09-03 Update README.md
    Updating README for release.

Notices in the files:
parts and their libraries:
SparkFun-Capacitors: Licensing: Creative Commons ShareAlike 4.0 International - https://creativecommons.org/licenses/by-sa/4.0
SparkFun-Aesthetics: Released under the Creative Commons Attribution Share-Alike 4.0 License
SparkFun-Aesthetics: https://creativecommons.org/licenses/by-sa/4.0
